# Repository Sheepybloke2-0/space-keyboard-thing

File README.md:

# A travel keyboard with space theme
A 40% travel keyboard with bluetooth

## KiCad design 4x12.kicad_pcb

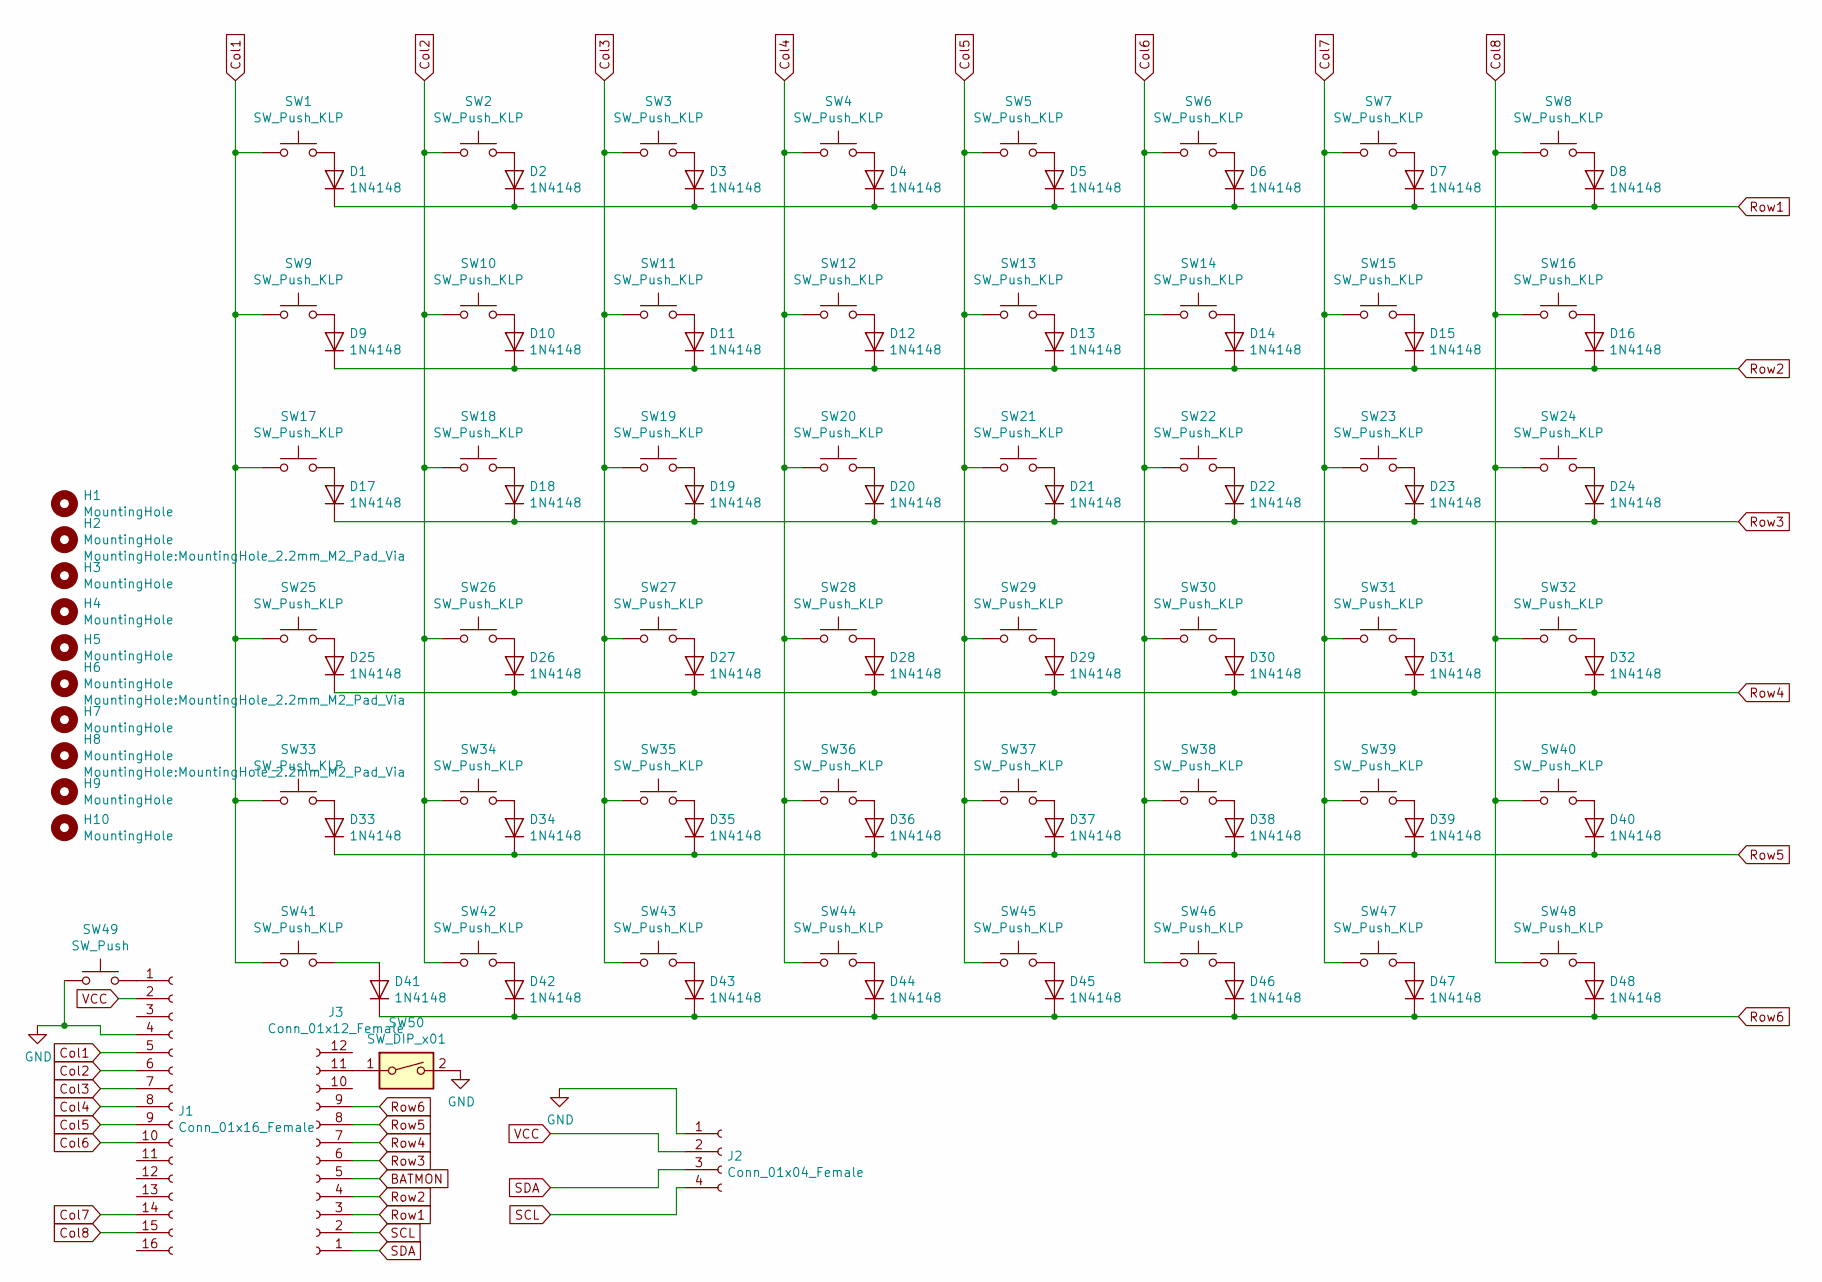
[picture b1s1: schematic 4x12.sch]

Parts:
D1, D2, D3, D4, D5, D6, D7, D8, D9, D10, D11, D12, D13, D14, D15, D16, D17, D18, D19, D20, D21, D22, D23, D24, D25, D26, D27, D28, D29, D30, D31, D32, D33, D34, D35, D36, D37, D38, D39, D40, D41, D42, D43, D44, D45, D46, D47, D48: 1N4148; D_DO-35_SOD27_P7.62mm_Horizontal
H1: MountingHole; MountingHole_2.2mm_M2_Pad
H2, H3, H4, H5, H6, H7, H8, H9, H10: MountingHole; MountingHole_2.2mm_M2_Pad_Via
J1: Conn_01x16_Female; PinSocket_1x17_P1.00mm_Vertical
J2: Conn_01x04_Female; PinHeader_1x04_P1.00mm_Vertical
J3: Conn_01x12_Female; PinSocket_1x12_P1.00mm_Vertical
SW1, SW2, SW3, SW4, SW5, SW6, SW7, SW8, SW9, SW10, SW11, SW12, SW13, SW14, SW15, SW16, SW17, SW18, SW19, SW20, SW21, SW22, SW23, SW24, SW25, SW26, SW27, SW28, SW29, SW30, SW31, SW32, SW33, SW34, SW35, SW36, SW37, SW38, SW39, SW40, SW41, SW42, SW43, SW44, SW45, SW46, SW47, SW48: SW_Push_KLP; Kailh-PG1350-1u-reversible
SW49: SW_Push; SW_Tactile_SPST_Angled_MJTP1117
SW50: SW_DIP_x01; SW_CuK_OS102011MA1QN1_SPDT_Angled

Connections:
BATMON: J3.5
Col1: J1.5, SW1.1, SW9.1, SW17.1, SW25.1, SW33.1, SW41.1
Col2: J1.6, SW2.1, SW10.1, SW18.1, SW26.1, SW34.1, SW42.1
Col3: J1.7, SW3.1, SW11.1, SW19.1, SW27.1, SW35.1, SW43.1
Col4: J1.8, SW4.1, SW12.1, SW20.1, SW28.1, SW36.1, SW44.1
Col5: J1.9, SW5.1, SW13.1, SW21.1, SW29.1, SW37.1, SW45.1
Col6: J1.10, SW6.1, SW14.1, SW22.1, SW30.1, SW38.1, SW46.1
Col7: J1.14, SW7.1, SW15.1, SW23.1, SW31.1, SW39.1, SW47.1
Col8: J1.15, SW8.1, SW16.1, SW24.1, SW32.1, SW40.1, SW48.1
GND: J1.4, J2.1, SW49.1, SW50.2
unnamed: D1.2 (A), SW1.2
unnamed: D2.2 (A), SW2.2
unnamed: D3.2 (A), SW3.2
unnamed: D4.2 (A), SW4.2
unnamed: D5.2 (A), SW5.2
unnamed: D6.2 (A), SW6.2
unnamed: D7.2 (A), SW7.2
unnamed: D8.2 (A), SW8.2
unnamed: D9.2 (A), SW9.2
unnamed: D10.2 (A), SW10.2
unnamed: D11.2 (A), SW11.2
unnamed: D12.2 (A), SW12.2
unnamed: D13.2 (A), SW13.2
unnamed: D14.2 (A), SW14.2
unnamed: D15.2 (A), SW15.2
unnamed: D16.2 (A), SW16.2
unnamed: D17.2 (A), SW17.2
unnamed: D18.2 (A), SW18.2
unnamed: D19.2 (A), SW19.2
unnamed: D20.2 (A), SW20.2
unnamed: D21.2 (A), SW21.2
unnamed: D22.2 (A), SW22.2
unnamed: D23.2 (A), SW23.2
unnamed: D24.2 (A), SW24.2
unnamed: D25.2 (A), SW25.2
unnamed: D26.2 (A), SW26.2
unnamed: D27.2 (A), SW27.2
unnamed: D28.2 (A), SW28.2
unnamed: D29.2 (A), SW29.2
unnamed: D30.2 (A), SW30.2
unnamed: D31.2 (A), SW31.2
unnamed: D32.2 (A), SW32.2
unnamed: D33.2 (A), SW33.2
unnamed: D34.2 (A), SW34.2
unnamed: D35.2 (A), SW35.2
unnamed: D36.2 (A), SW36.2
unnamed: D37.2 (A), SW37.2
unnamed: D38.2 (A), SW38.2
unnamed: D39.2 (A), SW39.2
unnamed: D40.2 (A), SW40.2
unnamed: D41.2 (A), SW41.2
unnamed: D42.2 (A), SW42.2
unnamed: D43.2 (A), SW43.2
unnamed: D44.2 (A), SW44.2
unnamed: D45.2 (A), SW45.2
unnamed: D46.2 (A), SW46.2
unnamed: D47.2 (A), SW47.2
unnamed: D48.2 (A), SW48.2
unnamed: J1.1, SW49.2
unnamed: J3.11, SW50.1
Row1: D1.1 (K), D2.1 (K), D3.1 (K), D4.1 (K), D5.1 (K), D6.1 (K), D7.1 (K), D8.1 (K), J3.3
Row2: D9.1 (K), D10.1 (K), D11.1 (K), D12.1 (K), D13.1 (K), D14.1 (K), D15.1 (K), D16.1 (K), J3.4
Row3: D17.1 (K), D18.1 (K), D19.1 (K), D20.1 (K), D21.1 (K), D22.1 (K), D23.1 (K), D24.1 (K), J3.6
Row4: D25.1 (K), D26.1 (K), D27.1 (K), D28.1 (K), D29.1 (K), D30.1 (K), D31.1 (K), D32.1 (K), J3.7
Row5: D33.1 (K), D34.1 (K), D35.1 (K), D36.1 (K), D37.1 (K), D38.1 (K), D39.1 (K), D40.1 (K), J3.8
Row6: D41.1 (K), D42.1 (K), D43.1 (K), D44.1 (K), D45.1 (K), D46.1 (K), D47.1 (K), D48.1 (K), J3.9
SCL: J2.4, J3.2
SDA: J2.3, J3.1
VCC: J1.2, J2.2

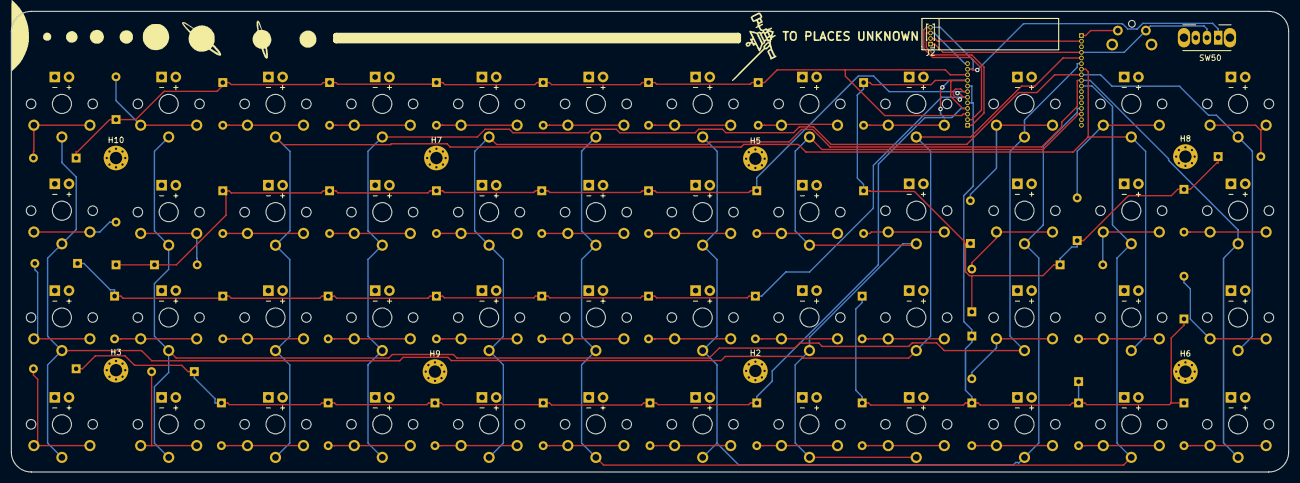
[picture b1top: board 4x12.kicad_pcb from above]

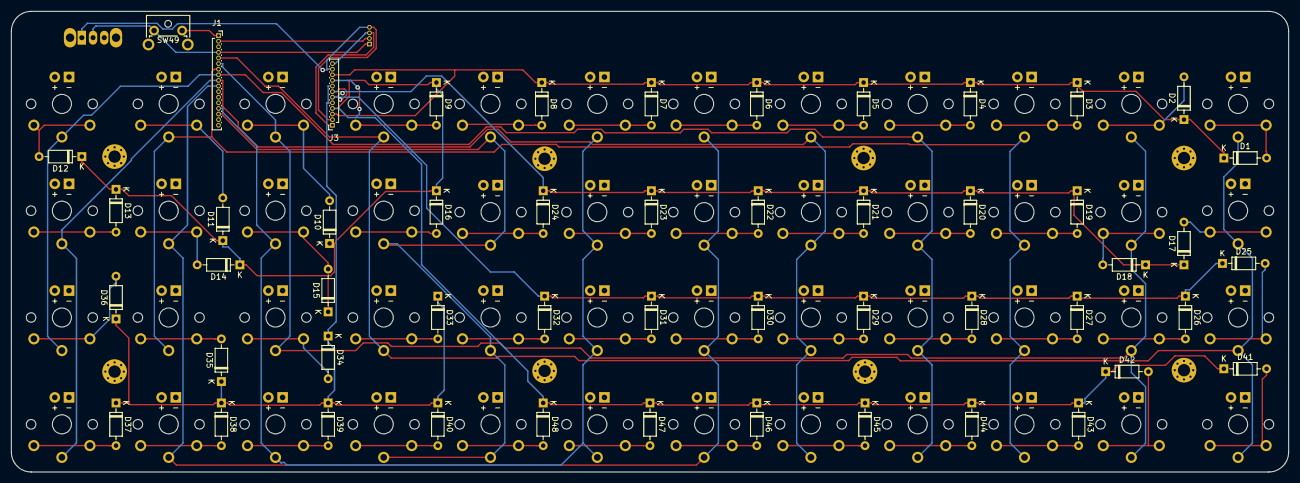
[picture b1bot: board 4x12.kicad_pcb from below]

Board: 2 copper layers, 227.8 x 82.2 mm, 111 parts (51 on the bottom side), 68 nets.

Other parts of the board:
Screen: screen; 3planets
Screen1: 1; voyager

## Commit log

2020-01-24 Added basic files to the repo.
2020-01-24 Added PDF with schematic and PCB,.
